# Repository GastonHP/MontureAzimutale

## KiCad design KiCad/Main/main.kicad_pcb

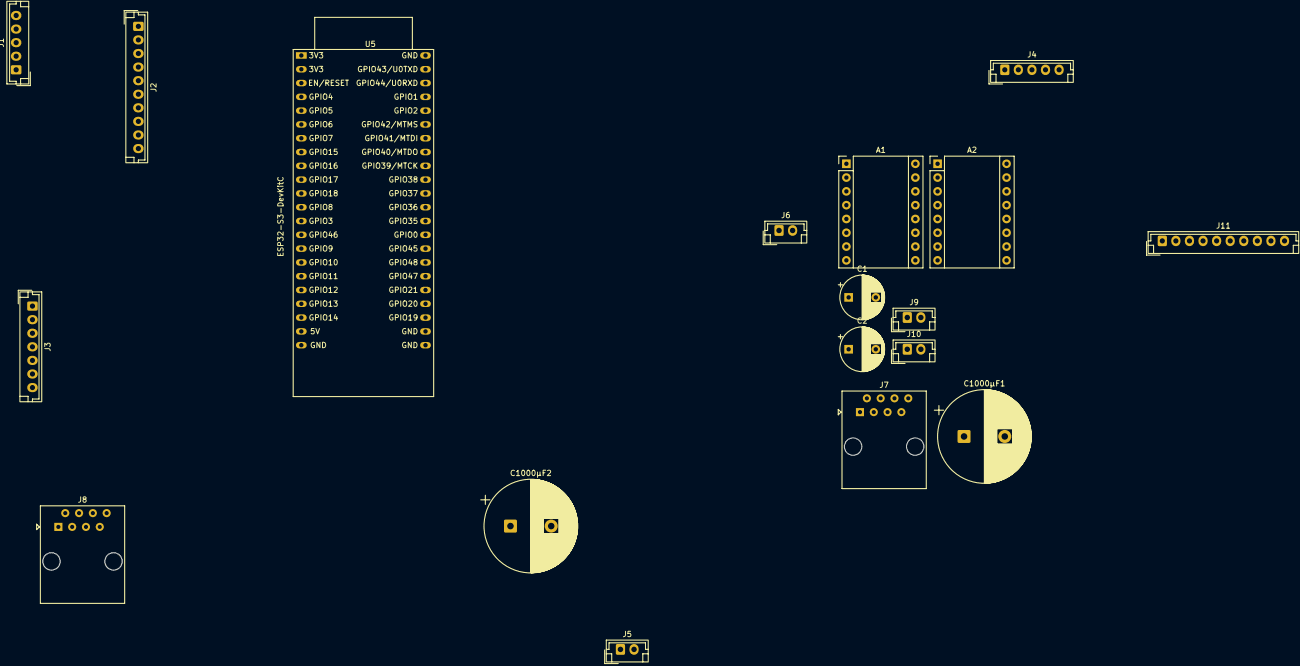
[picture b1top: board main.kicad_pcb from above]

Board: 2 copper layers, 18 parts (0 on the bottom side), 38 nets, no tracks yet.

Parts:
A1: Altitude; Pololu_Breakout-16_15.2x20.3mm
A2: Azimutal; Pololu_Breakout-16_15.2x20.3mm
C1, C2: 100µF; CP_Radial_D8.0mm_P5.00mm
C1000µF1, C1000µF2: C_Polarized; CP_Radial_D17.0mm_P7.50mm
J1, J4: Vers GPS; JST_EH_B5B-EH-A_1x05_P2.50mm_Vertical
J2: Vers Moteurs; JST_EH_B10B-EH-A_1x10_P2.50mm_Vertical
J3: Vers Display; JST_EH_B7B-EH-A_1x07_P2.50mm_Vertical
J5, J6, J9, J10: Conn_01x02_Pin; JST_EH_B2B-EH-A_1x02_P2.50mm_Vertical
J7, J8: RJ45; RJ45_Amphenol_54602-x08_Horizontal
J11: Conn_01x10_Pin; JST_EH_B10B-EH-A_1x10_P2.50mm_Vertical
U5: ESP32-S3-DevKitC

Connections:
/ALT/DIR: J2.10, U5.8 (GPIO15/ADC2_CH4/32K_P)
/ALT/STEP: J2.9, U5.7 (GPIO7/ADC1_CH6)
/AZ/DIR: J2.8, U5.6 (GPIO6/ADC1_CH5)
/AZ/STEP: J2.7, U5.5 (GPIO5/ADC1_CH4)
/CS: J3.1, U5.16 (GPIO10/ADC1_CH9)
/DC: J3.2, U5.4 (GPIO4/ADC1_CH3)
/EN: J2.6, U5.9 (GPIO16/ADC2_CH5/32K_N)
/GND: C1000µF2.2, J1.2, J2.1, J3.7, J5.1, J6.1, J8.7, U5.22 (GND), U5.23 (GND), U5.24 (GND), U5.44 (GND)
/M0: J2.2, U5.40 (GPIO2/ADC1_CH1)
/M1: J2.3, U5.38 (GPIO41/MTDI)
/M2: J2.4, U5.39 (GPIO42/MTMS)
/Moteurs et alimentation/5V: J9.2, J10.2
/Moteurs et alimentation/GND: J9.1, J10.1
/Moteurs/ALT/DIR: A1.16 (DIR), J11.10
/Moteurs/ALT/STEP: A1.15 (STEP), J11.9
/Moteurs/AZ/DIR: A2.16 (DIR), J11.8
/Moteurs/AZ/STEP: A2.15 (STEP), J11.7
/Moteurs/EN: A1.9 (~EN), A2.9 (~EN), J11.6
/Moteurs/GND: A1.1 (GND), A2.1 (GND), J11.1
/Moteurs/M0: A1.10 (M0), A2.10 (M0), J11.2
/Moteurs/M1: A1.11 (M1), A2.11 (M1), J11.3
/Moteurs/M2: A1.12 (M2), A2.12 (M2), J11.4
/Moteurs/RST/SLP: A1.13 (~RST), A1.14 (~SLP), A2.13 (~RST), A2.14 (~SLP), J11.5
/RST: J3.3, U5.20 (GPIO14/ADC2_CH3)
/RST/SLP: J2.5, U5.13 (GPIO3/ADC1_CH2)
/RXD: J1.4, U5.10 (GPIO17/ADC2_CH6)
/SCL: J8.6, U5.15 (GPIO9/ADC1_CH8)
/SCL_DSP: J3.5, U5.18 (GPIO12/ADC2_CH1)
/SDA: J8.5, U5.12 (GPIO8/ADC1_CH7)
/SDA_DSP: J3.4, U5.17 (GPIO11/ADC2_CH0)
/TXD: J1.3, U5.11 (GPIO18/ADC2_CH7)
/VCC: J1.1, J3.6, J8.8, U5.1 (3V3), U5.2 (3V3)
unnamed: A1.8 (VMOT), A2.8 (VMOT), C1.1, C2.1
unnamed: J5.2, J6.2
unnamed: A1.7 (GND), A2.7 (GND), C1.2, C2.2
unnamed: C1000µF2.1, U5.21 (5V)
unnamed: C1000µF1.2, J7.7
unnamed: C1000µF1.1, J7.8

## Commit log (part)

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2025-12-18 Fix spelling in project title
2025-12-31 lcd gmt020-02 ok
2026-01-02 bno08x ok
2026-01-03 gps, display et 3d sensor ok!
2026-01-03 yaw,roll et pitch ok
2026-01-06 nettoyage doc
2026-01-16 gps, display, accéléromètre : OK
2026-01-25 RGB_LED OK
2026-02-03 kicad ok
2026-02-24 partiel
2026-03-26 téléscope sans mvt moteurs OK
2026-04-22 ota webserver ok
2026-05-20 plante encore au calibrage mvt
2026-05-21 nettoyage display ok
2026-06-02 calibration ok
2026-06-15 bno085 et moteurs OK
2026-06-18 restructuration du repository
2026-06-29 capteur bno085 OK
2026-06-29 rename struct_message eb IMUData
2026-06-30 messages reçus
